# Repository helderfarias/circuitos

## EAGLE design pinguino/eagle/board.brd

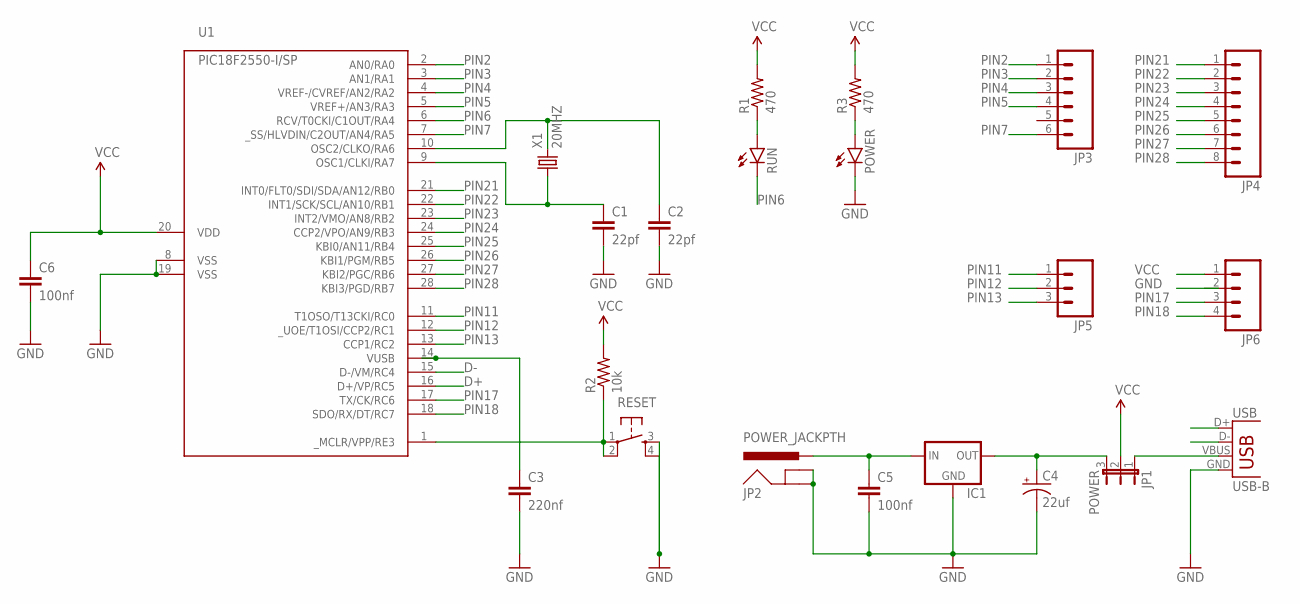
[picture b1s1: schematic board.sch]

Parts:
C1, C2: 22pf; CAP-PTH-SMALL-KIT
C3: 220nf; C050-050X075
C4: 22uf; CPOL-RADIAL-10UF-25V-KIT
C5, C6: 100nf; C050-050X075
IC1: 78XXL
JP1: POWER; JP2
JP2: POWER_JACKPTH; POWER_JACK_PTH
JP3: M06NO_SILK_YES_STOP; 1X06_NO_SILK_YES_STOP
JP4: M08NO_SILK_FEMALE_PTH; 1X08_NO_SILK
JP5: M031X03_NO_SILK; 1X03_NO_SILK
JP6: M04NO_SILK_ALL_ROUND; 1X04_NO_SILK_ALL_ROUND
POWER: LED3MM
R1, R3: 470; AXIAL-0.4
R2: 10k; AXIAL-0.4
RESET: TAC_SWITCHPTH; TACTILE-PTH
RUN: LED3MM
U1: PIC18F2550-I/SP; DIL28-3
USB: USB-B; USB-B-PTH
X1: 20MHZ; HC49

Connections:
D+: U1.16 (D+/VP/RC5), USB.D+
D-: U1.15 (D-/VM/RC4), USB.D-
GND: C1.2, C2.2, C3.2, C4.2 (-), C5.2, C6.2, IC1.GND, JP2.GND, JP2.GNDBREAK, POWER.K (C), RESET.3, RESET.4, U1.8 (VSS), U1.19 (VSS), USB.GND
unnamed: C2.1, U1.10 (OSC2/CLKO/RA6), X1.2
unnamed: C1.1, U1.9 (OSC1/CLKI/RA7), X1.1
unnamed: R1.P$1 (1), RUN.A
unnamed: R2.P$1 (1), RESET.1, RESET.2, U1.1 (_MCLR/VPP/RE3)
unnamed: POWER.A, R3.P$1 (1)
unnamed: C4.1 (+), IC1.OUT, JP1.3
unnamed: JP1.1, USB.VBUS
unnamed: C5.1, IC1.IN, JP2.PWR
PIN2: JP3.1, U1.2 (AN0/RA0)
PIN3: JP3.2, U1.3 (AN1/RA1)
PIN4: JP3.3, U1.4 (VREF-/CVREF/AN2/RA2)
PIN5: JP3.4, U1.5 (VREF+/AN3/RA3)
PIN6: RUN.K (C), U1.6 (RCV/T0CKI/C1OUT/RA4)
PIN7: JP3.6, U1.7 (_SS/HLVDIN/C2OUT/AN4/RA5)
PIN11: JP5.1, U1.11 (T1OSO/T13CKI/RC0)
PIN12: JP5.2, U1.12 (_UOE/T1OSI/CCP2/RC1)
PIN13: JP5.3, U1.13 (CCP1/RC2)
PIN14: C3.1, U1.14 (VUSB)
PIN17: JP6.3, U1.17 (TX/CK/RC6)
PIN18: JP6.4, U1.18 (SDO/RX/DT/RC7)
PIN21: JP4.1, U1.21 (INT0/FLT0/SDI/SDA/AN12/RB0)
PIN22: JP4.2, U1.22 (INT1/SCK/SCL/AN10/RB1)
PIN23: JP4.3, U1.23 (INT2/VMO/AN8/RB2)
PIN24: JP4.4, U1.24 (CCP2/VPO/AN9/RB3)
PIN25: JP4.5, U1.25 (KBI0/AN11/RB4)
PIN26: JP4.6, U1.26 (KBI1/PGM/RB5)
PIN27: JP4.7, U1.27 (KBI2/PGC/RB6)
PIN28: JP4.8, U1.28 (KBI3/PGD/RB7)
VCC: C6.1, JP1.2, JP6.1, R1.P$2 (2), R2.P$2 (2), R3.P$2 (2), U1.20 (VDD)

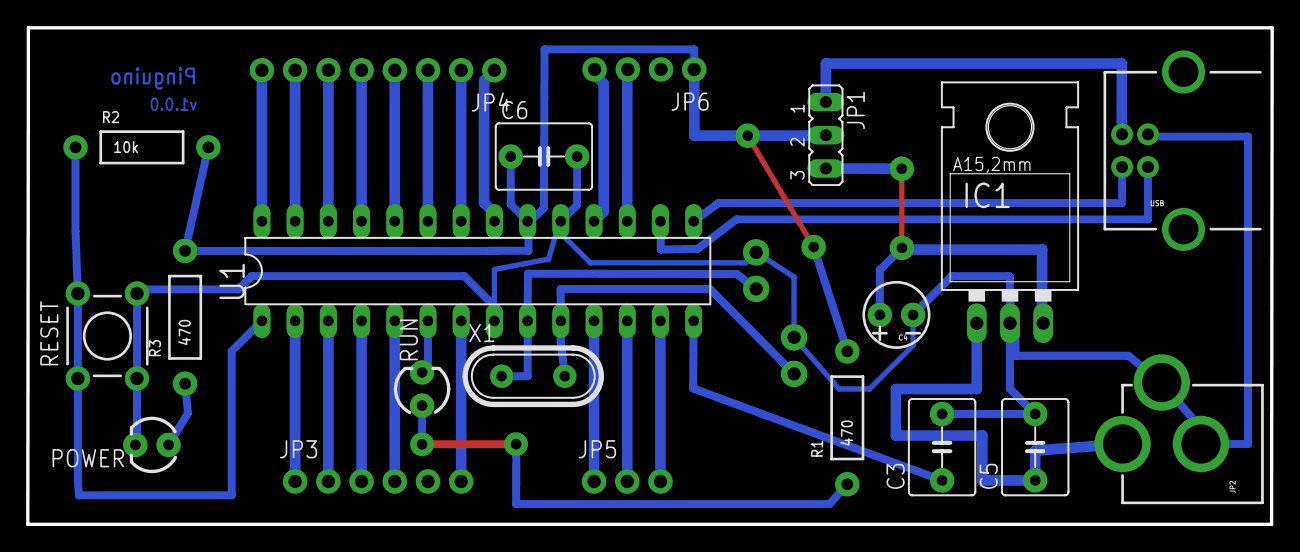
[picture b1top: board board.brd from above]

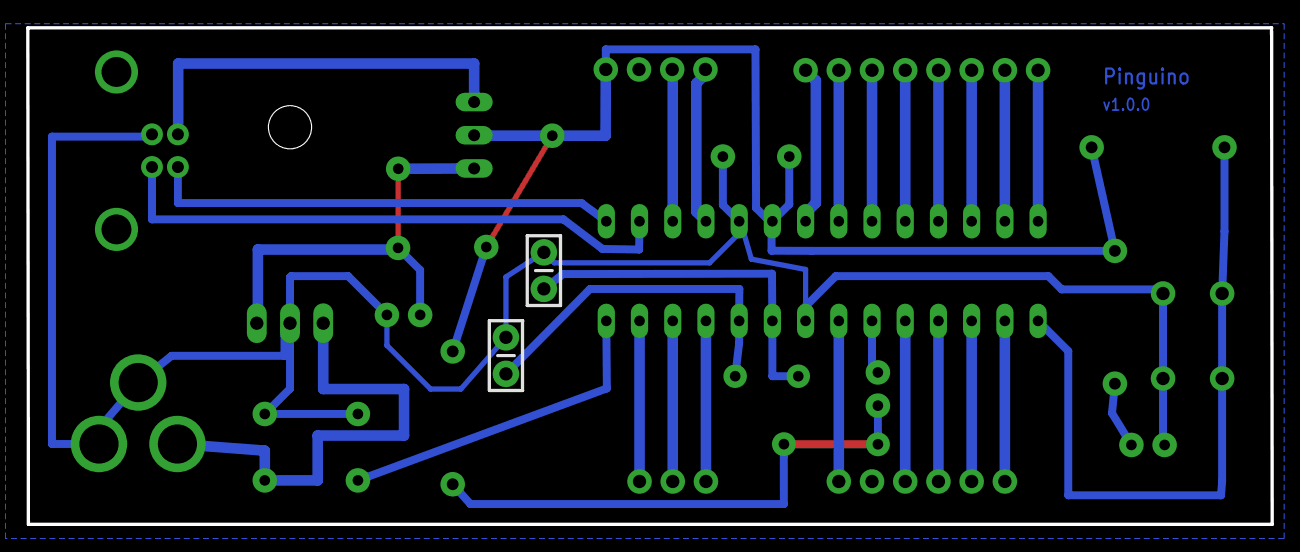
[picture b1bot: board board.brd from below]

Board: 2 copper layers, 95.2 x 38.0 mm, 22 parts (2 on the bottom side), 32 nets.

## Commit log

2015-07-29 import initial
2015-07-29 import inicial
2015-07-29 posionamento de perfuracoes
2015-07-31 projeto para eagle
2015-07-31 link
2015-08-01 pinguino board
2015-08-01 correcao de layout
2015-08-03 melhorias de layout
2015-08-03 melhoria
2015-08-03 menor proporcao
2015-08-10 remocao de projeto nao usado atualizando projeto final eagle

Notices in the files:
parts and their libraries:
SparkFun-Capacitors: Licensing: Creative Commons ShareAlike 4.0 International - https://creativecommons.org/licenses/by-sa/4.0
